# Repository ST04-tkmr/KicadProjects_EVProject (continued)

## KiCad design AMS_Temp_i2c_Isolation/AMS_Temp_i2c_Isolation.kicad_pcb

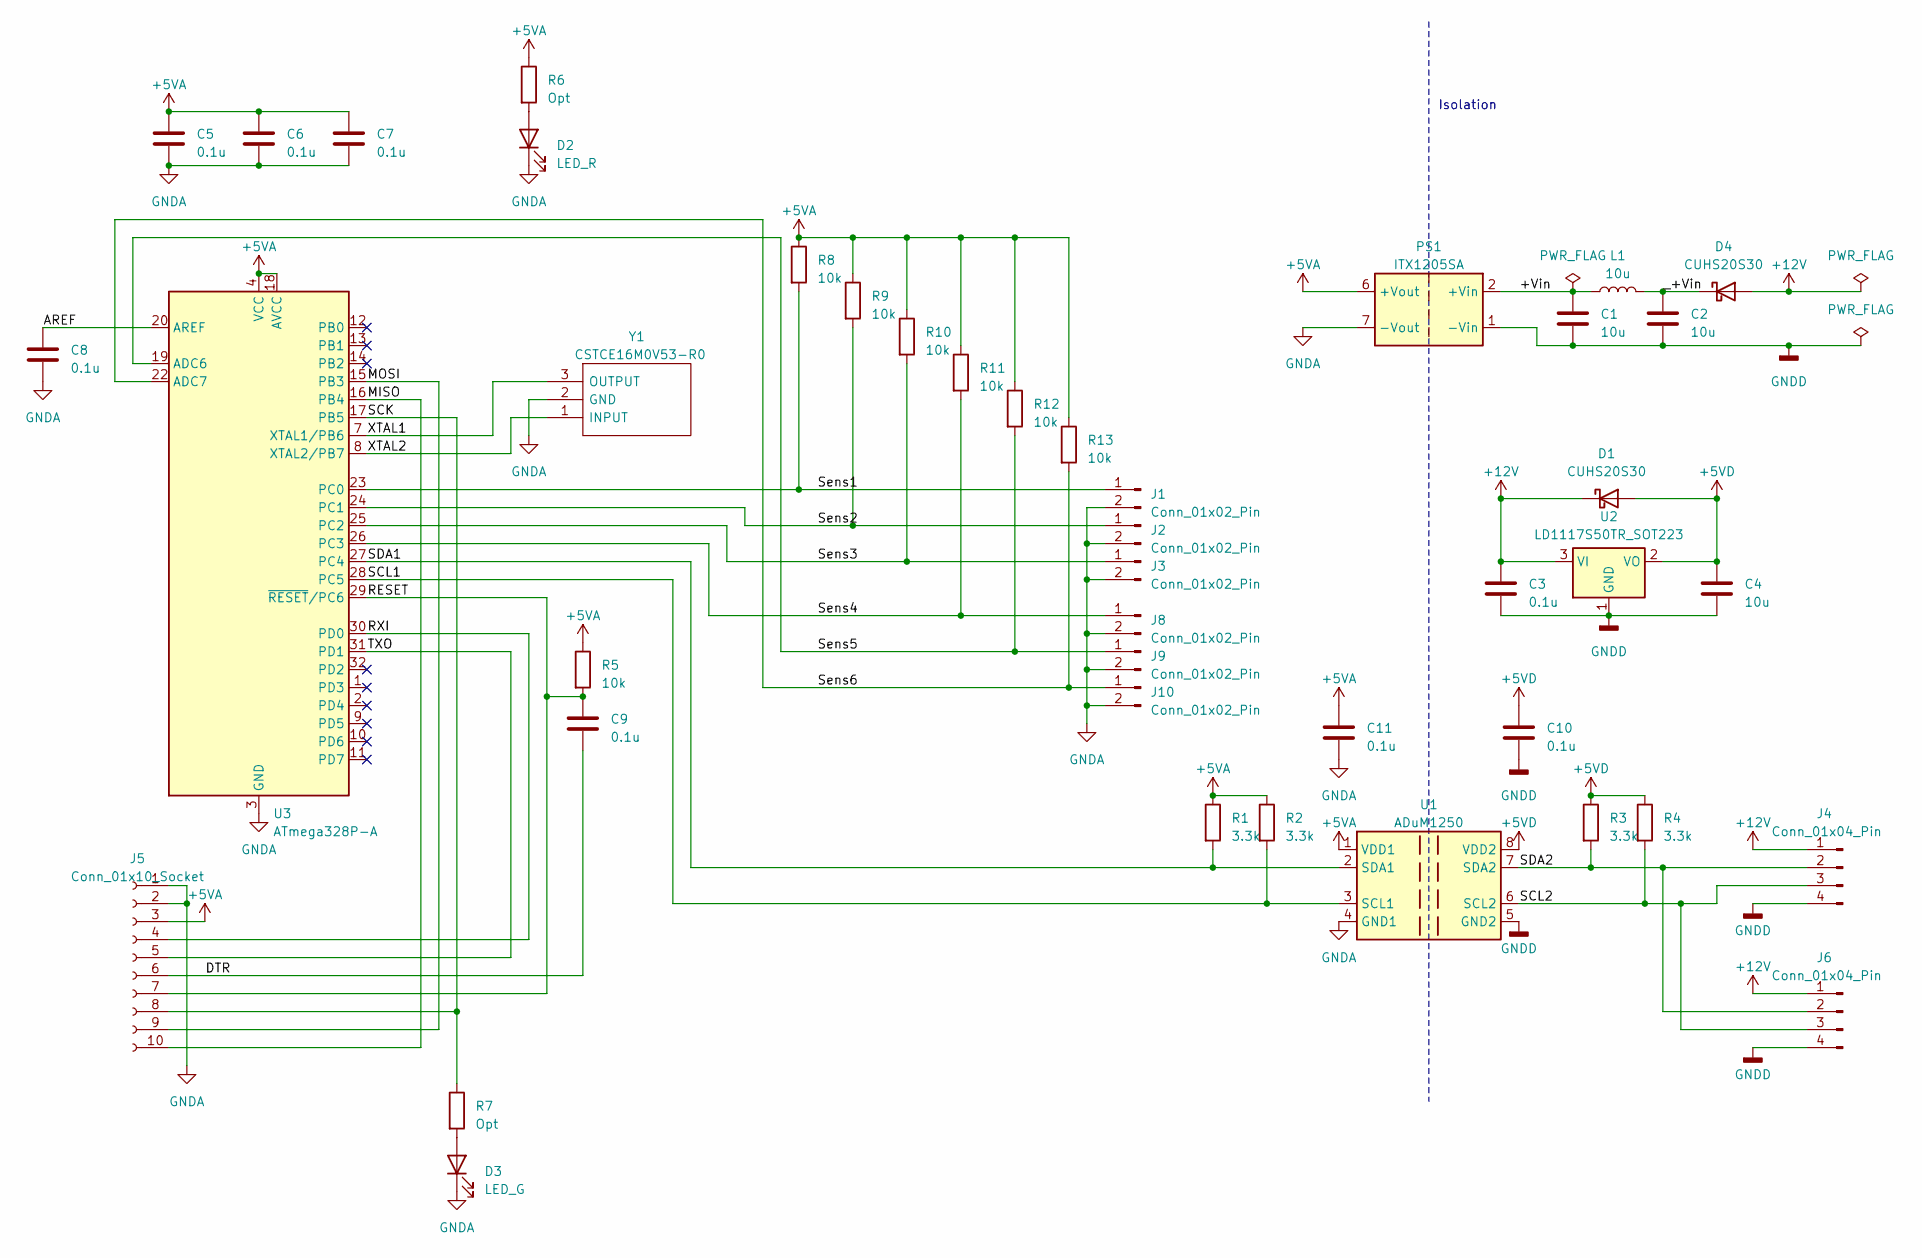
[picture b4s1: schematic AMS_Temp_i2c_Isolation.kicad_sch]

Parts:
C1, C2, C4: 10u; C_0603_1608Metric
C3, C5, C6, C7, C8, C9, C10, C11: 0.1u; C_0603_1608Metric
D1, D4: CUHS20S30; CUHS20S40H3F
D2: LED_R; LED_0603_1608Metric
D3: LED_G; LED_0603_1608Metric
J1, J2, J3, J8, J9, J10: Conn_01x02_Pin; JST_XH_S2B-XH-A_1x02_P2.50mm_Horizontal
J4: Conn_01x04_Pin; JST_XH_S4B-XH-A_1x04_P2.50mm_Horizontal
J5: Conn_01x10_Socket; PinSocket_1x10_P2.54mm_Vertical
J6: Conn_01x04_Pin; PinHeader_1x04_P2.54mm_Vertical
L1: 10u; L_Taiyo-Yuden_NR-10050_9.8x10.0mm
PS1: ITX1205SA; Converter_DCDC_XP_POWER-ITXxxxxSA_THT
R1, R2, R3, R4: 3.3k; R_0603_1608Metric
R5: 10k; R_0603_1608Metric
R6, R7: Opt; R_0603_1608Metric
R8, R9, R10, R11, R12, R13: 10k; R_0805_2012Metric
U1: ADuM1250; SOIC-8_3.9x4.9mm_P1.27mm
U2: LD1117S50TR_SOT223; SOT-223-3_TabPin2
U3: ATmega328P-A; TQFP-32_7x7mm_P0.8mm
Y1: CSTCE16M0V53-R0; CSTCE16M0V53R0; Manufacturer_Part_Number CSTCE16M0V53-R0; Mouser Part Number 81-CSTCE16M0V53-R0

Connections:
+5VA: C5.1, C6.1, C7.1, C11.1, J5.3, PS1.6 (+Vout), R1.1, R2.1, R5.1, R6.1, R8.1, R9.1, R10.1, R11.1, R12.1, R13.1, U1.1 (VDD1), U3.4 (VCC), U3.6 (VCC), U3.18 (AVCC)
+5VD: C4.1, C10.1, D1.2 (A), R3.1, R4.1, U1.8 (VDD2), U2.2 (VO)
+12V: C3.1, D1.1 (K), D4.2 (A), J4.1, J6.1, U2.3 (VI)
/+Vin: C1.1, L1.1, PS1.2 (+Vin)
/AREF: C8.1, U3.20 (AREF)
/DTR: C9.2, J5.6
/MISO: J5.10, U3.16 (PB4)
/MOSI: J5.9, U3.15 (PB3)
/RESET: C9.1, J5.7, R5.2, U3.29 (~RESET/PC6)
/RXI: J5.4, U3.30 (PD0)
/SCK: J5.8, R7.1, U3.17 (PB5)
/SCL1: R2.2, U1.3 (SCL1), U3.28 (PC5)
/SCL2: J4.3, J6.3, R4.2, U1.6 (SCL2)
/SDA1: R1.2, U1.2 (SDA1), U3.27 (PC4)
/SDA2: J4.2, J6.2, R3.2, U1.7 (SDA2)
/Sens1: J1.1, R8.2, U3.23 (PC0)
/Sens2: J2.1, R9.2, U3.24 (PC1)
/Sens3: J3.1, R10.2, U3.25 (PC2)
/Sens4: J8.1, R11.2, U3.26 (PC3)
/Sens5: J9.1, R12.2, U3.19 (ADC6)
/Sens6: J10.1, R13.2, U3.22 (ADC7)
/TXO: J5.5, U3.31 (PD1)
/XTAL1: U3.7 (XTAL1/PB6), Y1.3 (OUTPUT)
/XTAL2: U3.8 (XTAL2/PB7), Y1.1 (INPUT)
/_+Vin: C2.1, D4.1 (K), L1.2
GNDA: C5.2, C6.2, C7.2, C8.2, C11.2, D2.1 (K), D3.1 (K), J1.2, J2.2, J3.2, J5.1, J5.2, J8.2, J9.2, J10.2, PS1.7 (-Vout), U1.4 (GND1), U3.3 (GND), U3.5 (GND), U3.21 (GND), Y1.2 (GND)
GNDD: C1.2, C2.2, C3.2, C4.2, C10.2, J4.4, J6.4, PS1.1 (-Vin), U1.5 (GND2), U2.1 (GND)
unnamed: D2.2 (A), R6.2
unnamed: D3.2 (A), R7.2

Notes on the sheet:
Isolation

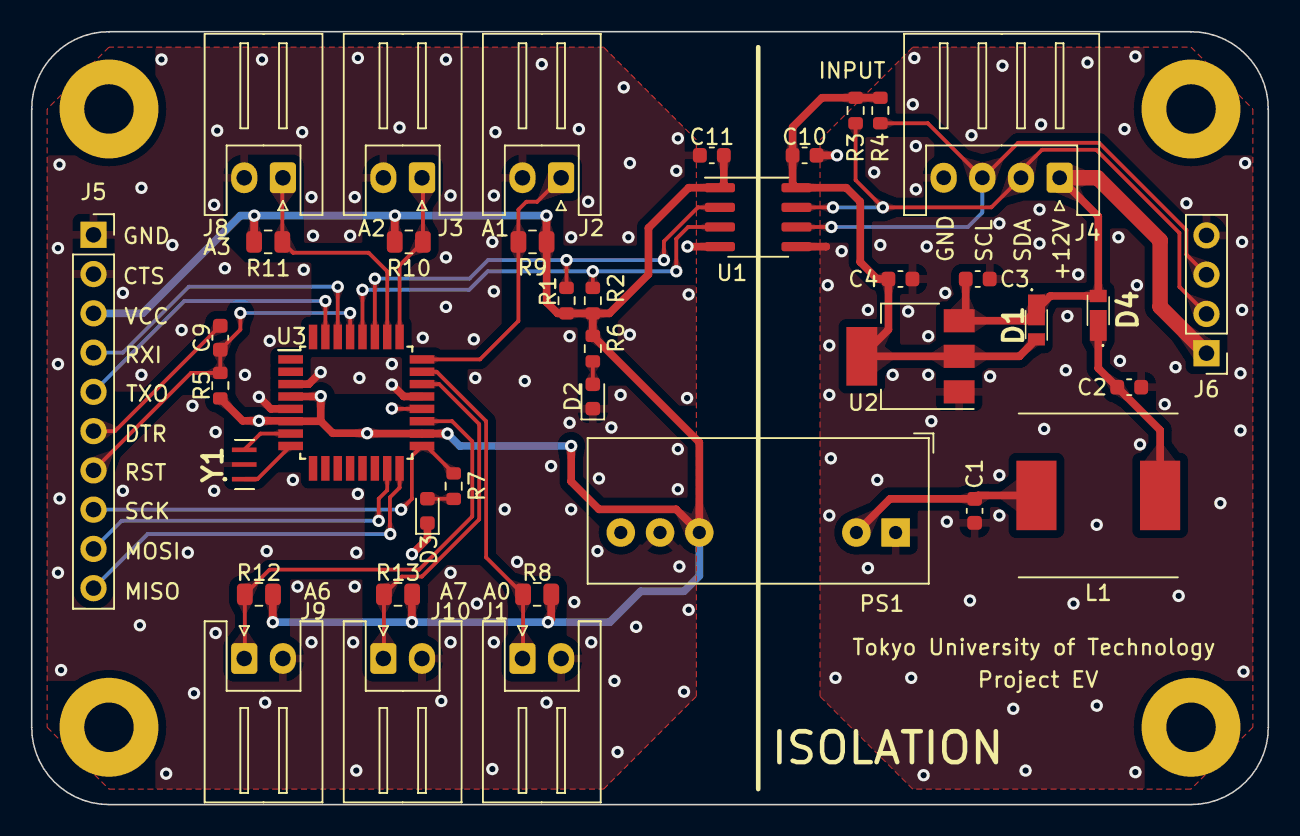
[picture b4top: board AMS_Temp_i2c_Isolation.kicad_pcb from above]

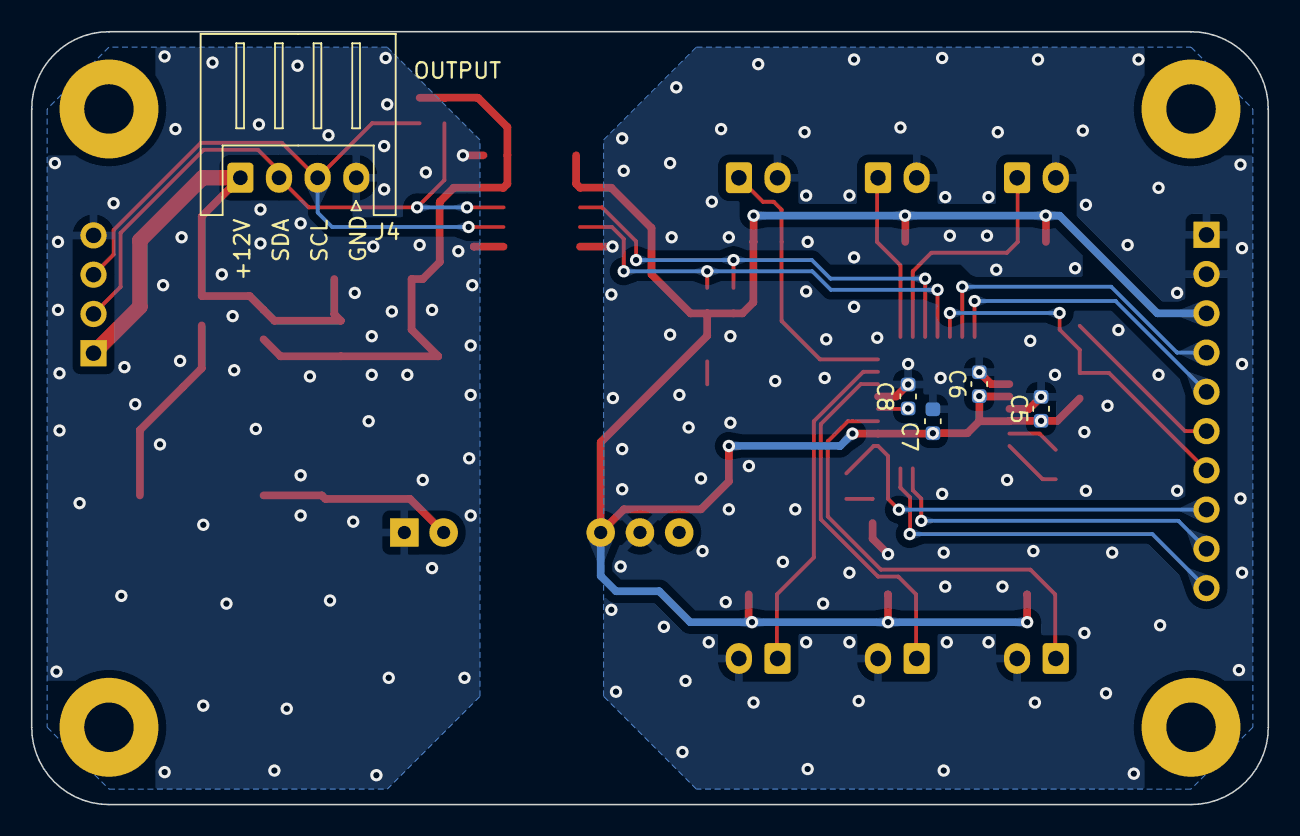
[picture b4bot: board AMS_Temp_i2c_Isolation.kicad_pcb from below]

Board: 2 copper layers, 80.0 x 50.0 mm, 44 parts (5 on the bottom side), 29 nets.

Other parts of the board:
J4#2: JST_XH_S4B-XH-A_1x04_P2.50mm_Horizontal_Silk

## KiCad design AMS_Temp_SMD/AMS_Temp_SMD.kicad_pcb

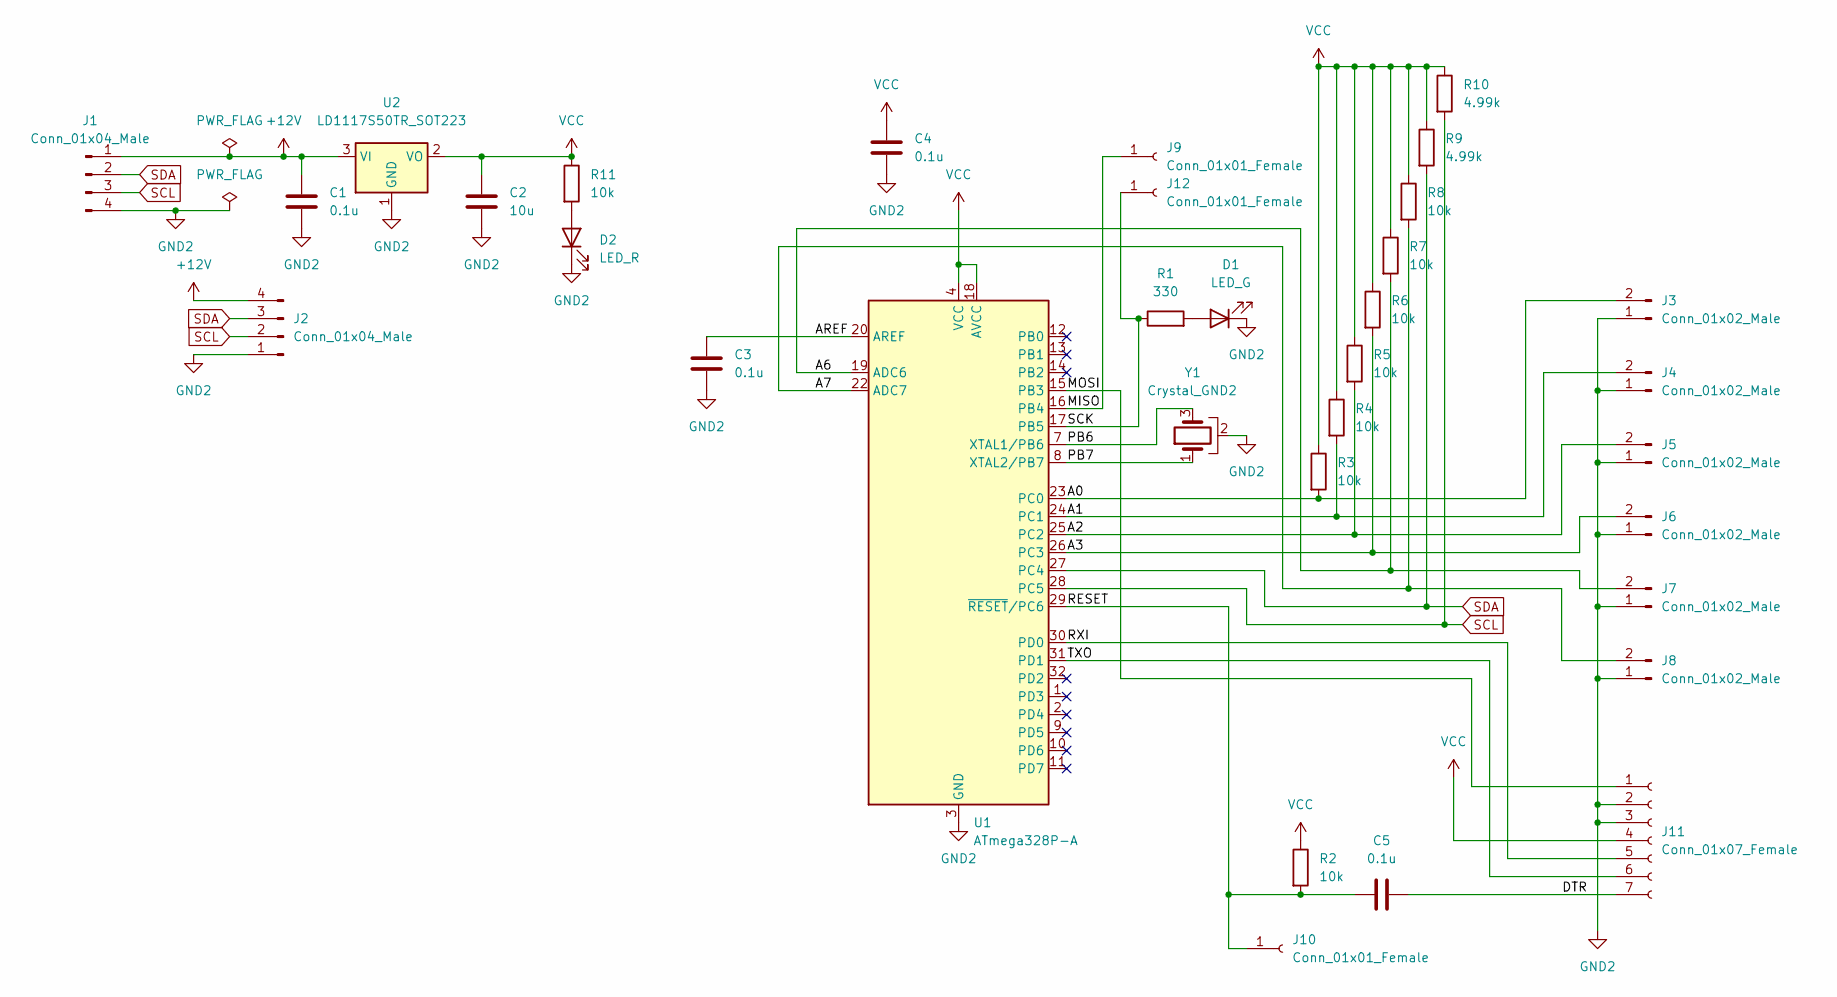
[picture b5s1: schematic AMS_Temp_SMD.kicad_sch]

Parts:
C1, C3, C4, C5: 0.1u; C_0603_1608Metric
C2: 10u; C_0805_2012Metric
D1: LED_G; LED_0603_1608Metric
D2: LED_R; LED_0603_1608Metric
J1, J2: Conn_01x04_Male; JST_XH_S4B-XH-A_1x04_P2.50mm_Horizontal
J3, J4, J5, J6, J7, J8: Conn_01x02_Male; JST_XH_S2B-XH-A_1x02_P2.50mm_Horizontal
J9, J10, J12: Conn_01x01_Female; PinSocket_1x01_P2.54mm_Horizontal
J11: Conn_01x07_Female; PinSocket_1x07_P2.54mm_Horizontal
R1: 330; R_0603_1608Metric
R2, R3, R4, R5, R6, R7, R8, R11: 10k; R_0805_2012Metric
R9, R10: 4.99k; R_0603_1608Metric
U1: ATmega328P-A; TQFP-32_7x7mm_P0.8mm
U2: LD1117S50TR_SOT223; SOT-223-3_TabPin2
Y1: Crystal_GND2; CSTCE16M0V53R0

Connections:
+12V: C1.1, J1.1, J2.4, U2.3 (VI)
/A0: J3.2, R3.2, U1.23 (PC0)
/A1: J4.2, R4.2, U1.24 (PC1)
/A2: J5.2, R5.2, U1.25 (PC2)
/A3: J6.2, R6.2, U1.26 (PC3)
/A6: J7.2, R7.2, U1.19 (ADC6)
/A7: J8.2, R8.2, U1.22 (ADC7)
/AREF: C3.2, U1.20 (AREF)
/DTR: C5.2, J11.7
/MISO: J9.1, U1.16 (PB4)
/MOSI: J11.1, U1.15 (PB3)
/PB6: U1.7 (XTAL1/PB6), Y1.3
/PB7: U1.8 (XTAL2/PB7), Y1.1
/RESET: C5.1, J10.1, R2.2, U1.29 (~RESET/PC6)
/RXI: J11.5, U1.30 (PD0)
/SCK: J12.1, R1.1, U1.17 (PB5)
/TXO: J11.6, U1.31 (PD1)
GND2: C1.2, C2.2, C3.1, C4.1, D1.1 (K), D2.1 (K), J1.4, J2.1, J3.1, J4.1, J5.1, J6.1, J7.1, J8.1, J11.2, J11.3, U1.3 (GND), U1.5 (GND), U1.21 (GND), U2.1 (GND), Y1.2
unnamed: D1.2 (A), R1.2
unnamed: D2.2 (A), R11.2
SCL: J1.3, J2.2, R10.2, U1.28 (PC5)
SDA: J1.2, J2.3, R9.2, U1.27 (PC4)
VCC: C2.1, C4.2, J11.4, R2.1, R3.1, R4.1, R5.1, R6.1, R7.1, R8.1, R9.1, R10.1, R11.1, U1.4 (VCC), U1.6 (VCC), U1.18 (AVCC), U2.2 (VO)

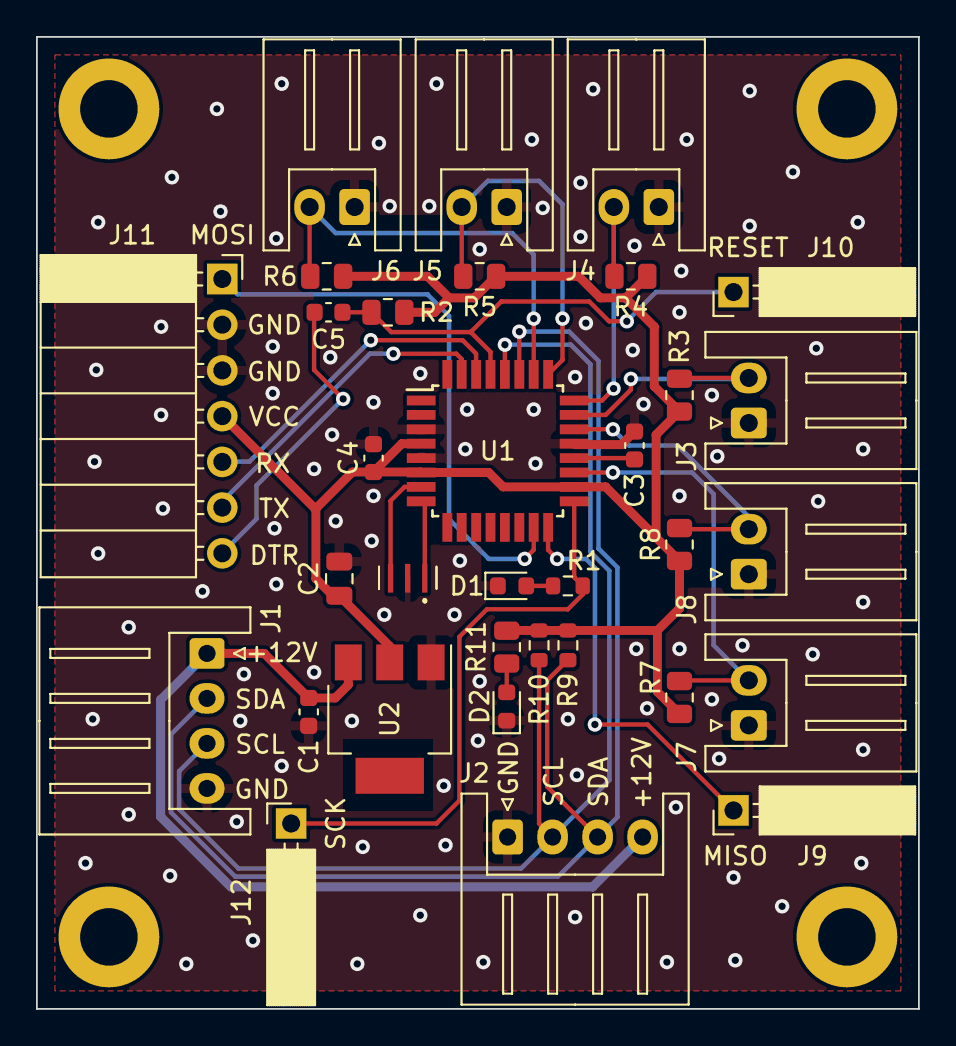
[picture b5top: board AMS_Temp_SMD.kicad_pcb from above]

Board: 2 copper layers, 49.0 x 54.0 mm, 33 parts (0 on the bottom side), 23 nets.

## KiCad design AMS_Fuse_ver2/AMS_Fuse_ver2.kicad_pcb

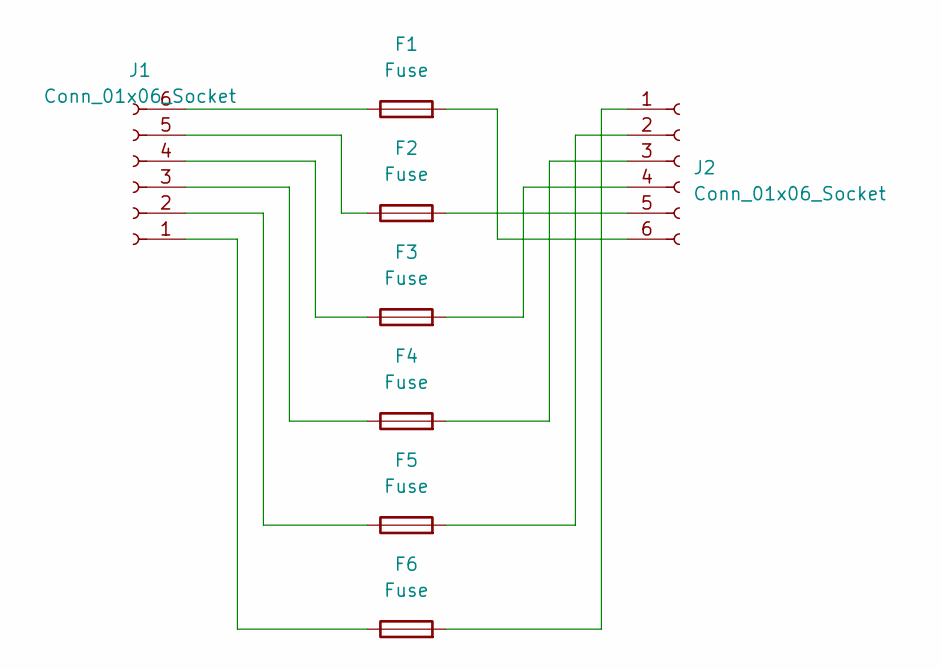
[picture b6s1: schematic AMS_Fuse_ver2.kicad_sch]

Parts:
F1, F2, F3, F4, F5, F6: Fuse; F-60-A
J1, J2: Conn_01x06_Socket; JST_XH_S6B-XH-A_1x06_P2.50mm_Horizontal

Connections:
unnamed: F6.1, J1.1
unnamed: F5.1, J1.2
unnamed: F4.1, J1.3
unnamed: F3.1, J1.4
unnamed: F2.1, J1.5
unnamed: F1.1, J1.6
unnamed: F6.2, J2.1
unnamed: F5.2, J2.2
unnamed: F4.2, J2.3
unnamed: F3.2, J2.4
unnamed: F2.2, J2.5
unnamed: F1.2, J2.6

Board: 2 copper layers, 8 parts (0 on the bottom side), 12 nets, no tracks yet.

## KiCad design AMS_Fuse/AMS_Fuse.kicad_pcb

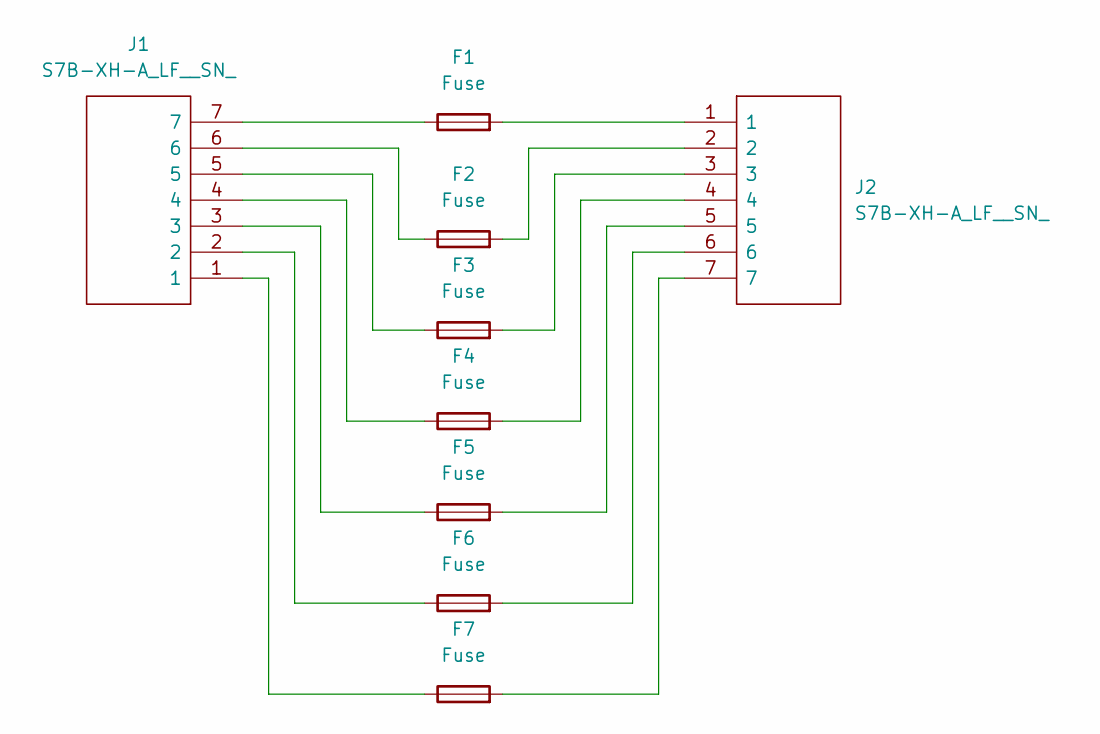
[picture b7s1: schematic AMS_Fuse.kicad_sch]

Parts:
F1, F2, F3, F4, F5, F6, F7: Fuse; F-60-A
J1, J2: S7B-XH-A_LF__SN_; SHDRRA7W64P0X250_1X7_1990X1150X610P; Manufacturer_Part_Number S7B-XH-A(LF)(SN)

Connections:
unnamed: F1.1, J1.7
unnamed: F1.2, J2.1
unnamed: F2.1, J1.6
unnamed: F2.2, J2.2
unnamed: F3.1, J1.5
unnamed: F3.2, J2.3
unnamed: F4.1, J1.4
unnamed: F4.2, J2.4
unnamed: F5.1, J1.3
unnamed: F5.2, J2.5
unnamed: F6.1, J1.2
unnamed: F6.2, J2.6
unnamed: F7.1, J1.1
unnamed: F7.2, J2.7

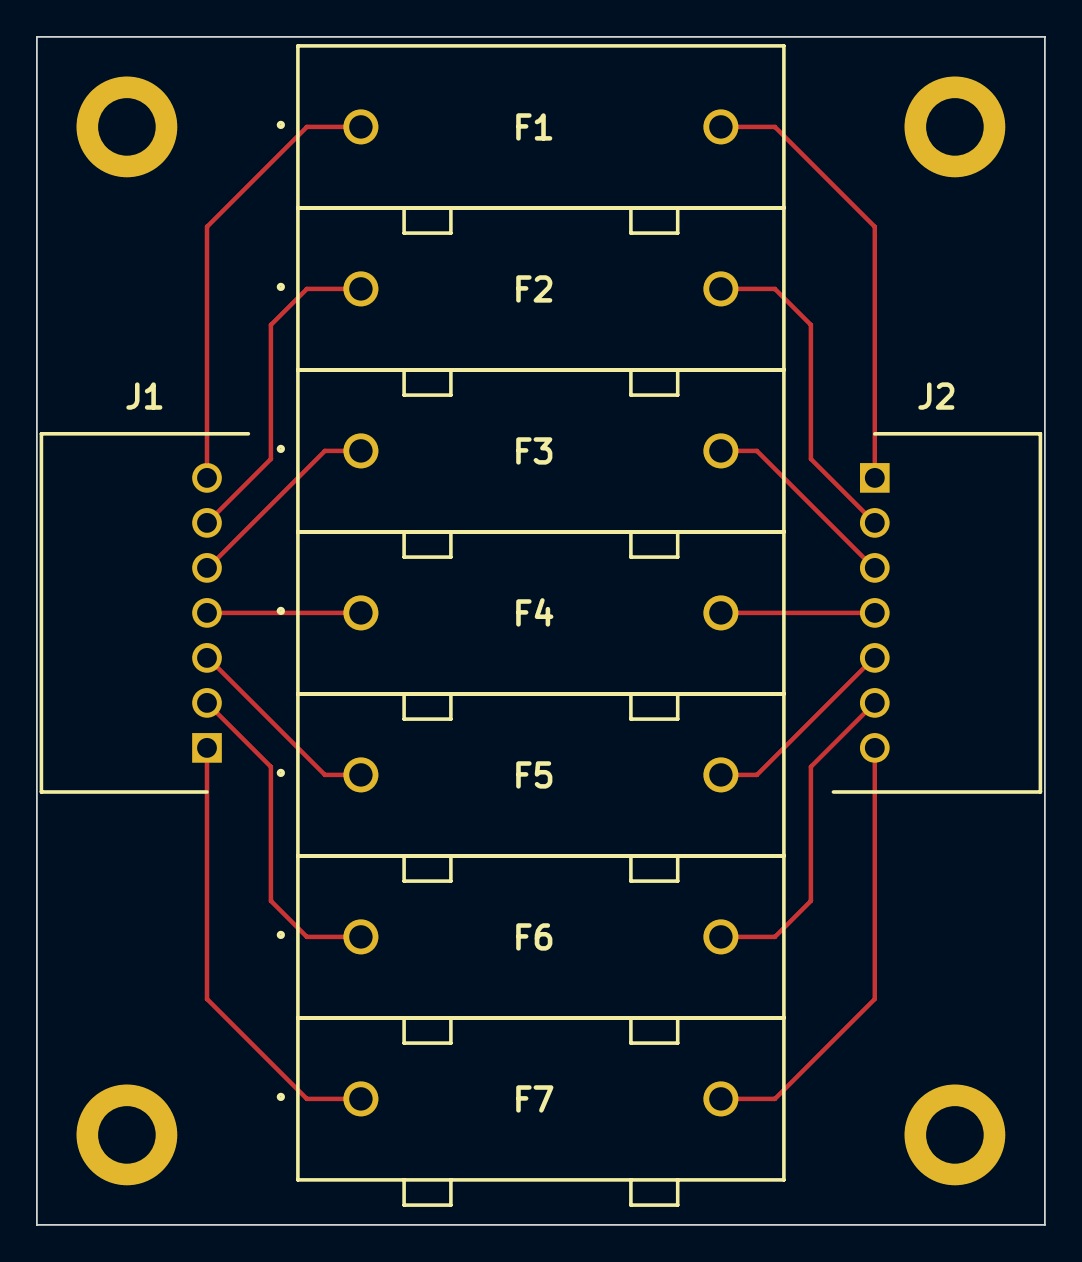
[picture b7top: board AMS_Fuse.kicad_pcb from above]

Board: 2 copper layers, 56.0 x 66.0 mm, 9 parts (0 on the bottom side), 14 nets.

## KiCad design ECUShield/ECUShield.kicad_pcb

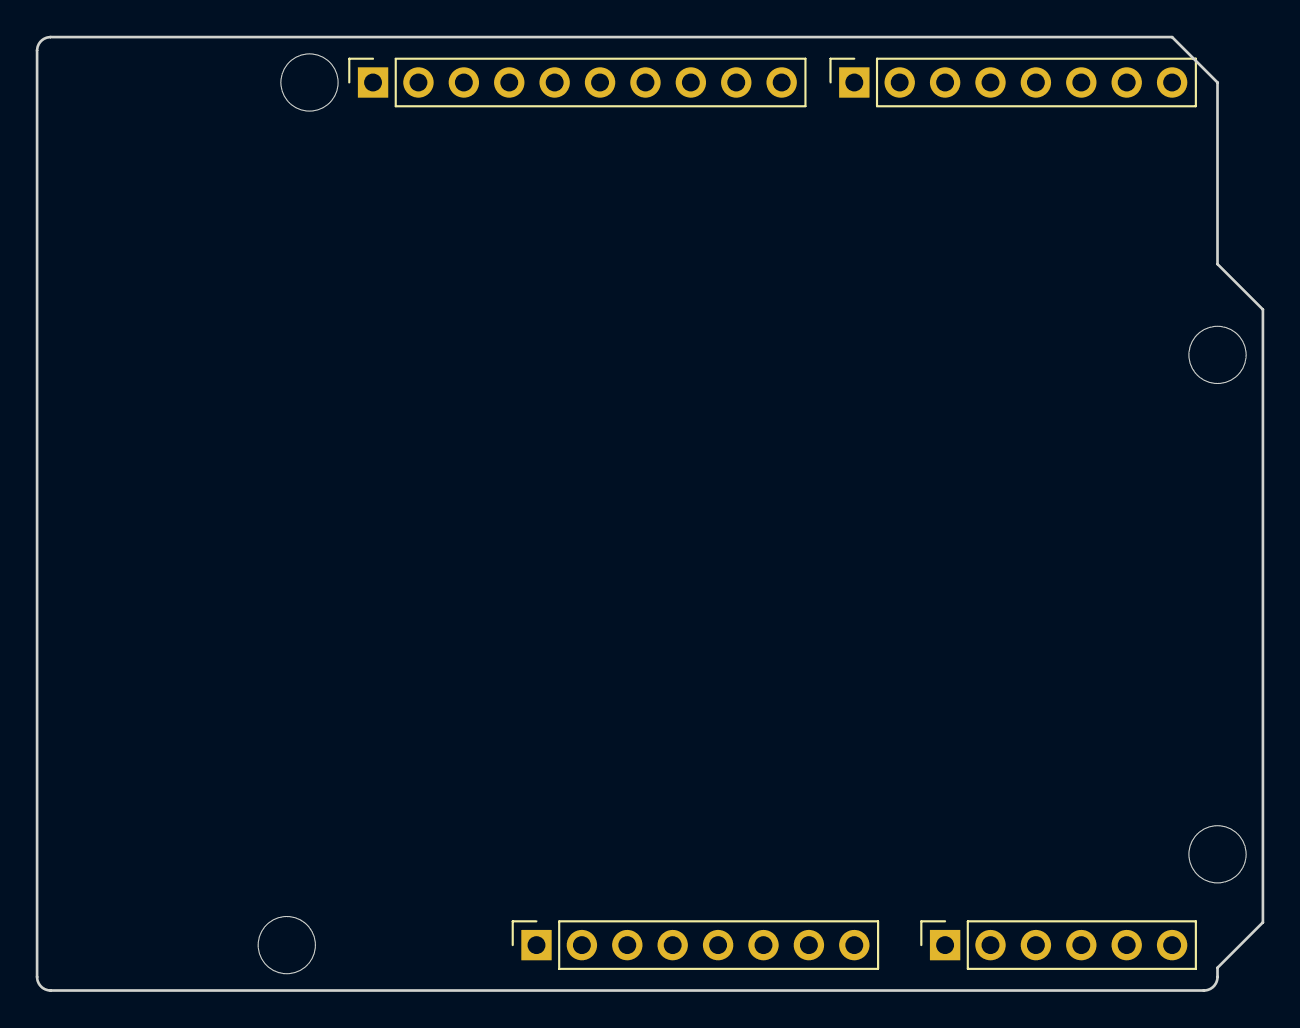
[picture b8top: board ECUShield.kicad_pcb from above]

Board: 2 copper layers, 68.6 x 53.3 mm, 8 parts (0 on the bottom side), 3 nets, no tracks yet.

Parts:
J1: Power; PinSocket_1x08_P2.54mm_Vertical
J2: Digital/PWM; PinSocket_1x10_P2.54mm_Vertical
J3: Analog; PinSocket_1x06_P2.54mm_Vertical
J4: Digital/PWM; PinSocket_1x08_P2.54mm_Vertical
MH1, MH2, MH3, MH4: MountingHole_3.2mm

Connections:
/SCL/A5: J2.1, J3.6
/SDA/A4: J2.2, J3.5
GND: J1.6, J1.7, J2.4

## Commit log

2023-03-19 プロジェクト追加
2023-03-19 位置修正
2023-03-19 modify
2023-03-23 AMS更新
2023-03-23 AMS_Master更新
2023-03-24 AMS_Master回路図作成
2023-03-27 AMS_Master回路図更新
2023-03-31 回路図更新
2023-04-03 AMS_Master
2023-04-19 CANコネクタ, pull up抵抗追加
2023-06-01 新規追加と修正
2023-06-01 回路図作成
2023-06-02 温度監視回路図作成
2023-06-02 close 20230602_16:05
2023-06-02 Complete AMS_Temp_Master Circuit Schematics and modify
2023-06-05 部品配置
2023-06-11 回路図修正, パターン作成
2023-06-12 パターン作成
2023-06-15 修正とパターン完成
2023-06-18 modify and complete
2023-06-18 ベタ表面修正
2023-06-27 add project and create schematic
2023-06-27 pcb design start
2023-06-28 残りはベタ修正
2023-06-29 pcb修正
2023-07-02 パターン設計ほぼ完了
2023-07-04 完成、これで発注予定
2023-07-04 修正、ティアドロップ追加
2023-07-04 完成, 発注
2023-07-04 更新, 変更なし
2023-07-04 シルク修正, 発注
2023-07-06 修正と追加
2023-07-06 回路図修正
2023-07-07 回路図作成, パターン作成途中
2023-07-07 基板配置まで
2023-07-08 パターン設計途中
2023-07-08 不要ファイル削除, スリットなし
2023-07-08 パターン作成途中
2023-07-10 finish, ver1
2023-07-10 finish, ver2
2023-07-10 modify, finish, ver3
2023-07-11 回路図修正, パターン再設計
2023-07-12 パターン再設計完了, 寝かせ
2023-07-13 修正版寝かせ
2023-07-13 10k抵抗フットプリント修正2012
2023-07-14 最終確認, ガーバーand bom出力
2023-07-20 回路図微修正
